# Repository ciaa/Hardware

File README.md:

Hardware
========

CIAA Hardware repository. It contains KiCad project files and documentation for each CIAA profile.

Folder structure:

[Doc](Doc): Common documents.

[PCB](PCB): KiCad PCB project files.

--[CIAA-ACC](PCB/ACC/CIAA_ACC): Xilinx Zynq XC7Z030 files.

--[EDU-FSL](PCB/EDU-FSL): EDU-CIAA-FSL (K60 MCU) files.

--[EDU-INTEL](PCB/EDU-INTEL): EDU-CIAA-INTEL (SOM Edison) files.

--[EDU-NXP](PCB/EDU-NXP): EDU-CIAA-NXP (LPC4337 MCU) files.

--[EDU-XILINX](PCB/EDU-XILINX): EDU-CIAA-XILINX (Artix7 FPGA) files.

--[FSL-MINI](PCB/FSL-MINI): CIAA-Freescale (K60 MCU) files.

--[FSL](PCB/FSL): CIAA-Freescale (K60 MCU) files.

--[NXP](PCB/NXP): CIAA-NXP (LPC4337 MCU) files.

--[PIC](PCB/PIC): CIAA-PIC (PIC32 MCU) files.

--[RX](PCB/RX): CIAA-Renesas files.

--[Safety](PCB/Safety): CIAA-Safety (RM48L952-PGE MCU) files.

--[Z3R0](PCB/Z3R0): CIAA-Z3R0 (EFM32HG MCU) files.

--[pico-CIAA](PCB/pico): pico-CIAA (LPC54102 MCU) files.

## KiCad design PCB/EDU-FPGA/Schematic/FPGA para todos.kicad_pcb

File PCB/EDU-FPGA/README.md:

# EDU-CIAA-FPGA

Here you will find KiCad design files, gerber files and documentation for this board developed by Embedded Systems application group from [UTN FR Haedo](http://www.frh.utn.edu.ar/) as part of the [CIAA project](http://www.proyecto-ciaa.com.ar/).
Also you can visit [EDU-CIAA-FPGA Wiki Page](http://www.proyecto-ciaa.com.ar/devwiki/doku.php?id=desarrollo:edu-fpga).

 - [Authors](AUTHORS.md).
 - License: [CIAA Hardware license](LICENSE).
 
## Buy the board!

The board can be acquired through Mercado Libre ecommerce platform:

 - [Option A: One payment](https://articulo.mercadolibre.com.ar/MLA-876444808-placa-desarrollo-edu-fpga-lattice-ice40hx4k-_JM#position=1&type=item&tracking_id=b1710986-8dfb-414d-ae1f-01746e770309)
 - [Option B: Pay in installments](https://articulo.mercadolibre.com.ar/MLA-878714026-placa-desarrollo-edu-fpga-lattice-ice40hx4k-cuotas-sin-int-_JM#position=2&type=item&tracking_id=b1710986-8dfb-414d-ae1f-01746e770309)
 
The board has been manufactured and is guaranteed by [Outsource SRL](http://www.outsourcesrl.com/)

## Links of interest

* [Official web page (in Spanish)](https://bit.ly/EDUFPGAok)
* [Youtube channel (in Spanish)](https://bit.ly/EDUFPGAyoutube)
* [Wiki (in Spanish)](https://bit.ly/EDUFPGAwiki)
 
## Board description

EDU-FPGA is an open source FPGA development board based on [Lattice iCE40HX4K](http://www.latticesemi.com/iCE40), and is part of **FPGA Para Todos** project, which is aimed to bring educational resources for FPGA technologies. EDU-FPGA supports [IceStorm](http://www.clifford.at/icestorm/) open source toolchain and is designed to be a low cost solution for beginners and intermediate students or professionals who wants to start studying FPGA's technologies or deepen their knowledges on this field. Currently, there are two versions of the board: v1.0 and v1.2. The following image shows both:

The board on the right is v1.2 (last version), and it has improvements on smd oscillator, USB footprint, flash memory and push-buttons, to make it more suitable for manufacture. 

More resources and information about **FPGA Para Todos** can be found on project's Wiki [here](https://gitlab.com/RamadrianG/wiki---fpga-para-todos/-/wikis/FPGA-para-Todos).

## Specifications

* Lattice iCE40HX4K FPGA (8K LUT using icestorm toolchain)
* Virtual COM port for debugging and general purpose
* NOR Flash spiFlash, 4M-bit, 4Kb Uniform Sector 
* 4 user push buttons
* 4 user leds
* 2 PMOD 2x6 interfaces
* Similar pinout than Arduino one
* Total 49 I/O pins available for the user
* 12MHz 25ppm -40C +85C clock oscillator
* USB power supply
* 80x60 cm size

### Board Arquitecture

FPGA specifications:

| **Lattice iCE40HX4K TQ144**        |**Specs**|
| ---------------------------------- | ------- |
| Logic cells                        | 3520    |
| 4Kbits Blockrams                   | 20      |
| Phase Locking Loops (PLL)          | 2       |
| DSP slices                         | No      |
| I/O pins                           | 95      |
| Differential I/O pins              | 12      |
| Package                            | TQ144   |
| Price                              | 6 USD   |

## Project directory structure

### Pinout
[Pinout diagram](Pinout/Pinout%20EDU%20FPGA.pdf) of EDU-FPGA v1.2
### Images
Contains images resources for the repository

### Schematic
Here you can find design files, like *.pro, *.sch, *.kicad_pcb. *-cache.lib, *-rescue.lib, footprints lib table, symbols lib table, [schematic.pdf](Schematic/schematic.pdf). Also, under this directory you can find:

#### BOM
[BOM of EDU-FPGA v1.2 ](Schematic/BOM/BOM.ods)

#### footprints.3dshapes
3D shapes of components

#### footprints.pretty
Footprints of all components

#### Gerbers
[Gerbers files of EDU-FPGA v1.2](Schematic/Gerbers)

#### Libraries
Libraries of component's symbols created specifically for the project

#### Panellised
Soon, 4x4 panel of EDU-FPGA v1.2 will be available in this directory.
<!--Here you can also find [Gerbers](Schematic/Panelizado/V1.2/Gerbers) of 4x4 panel.-->

#### Simbolos_EDUFPGA.pretty
Symbols of EDU-FPGA project logo

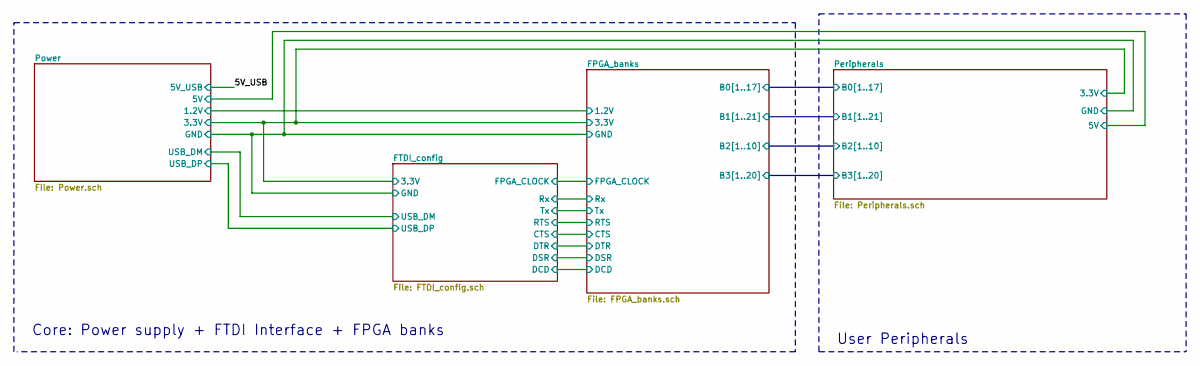
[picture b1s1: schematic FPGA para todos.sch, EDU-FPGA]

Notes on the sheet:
Core: Power supply + FTDI Interface + FPGA banks
User Peripherals

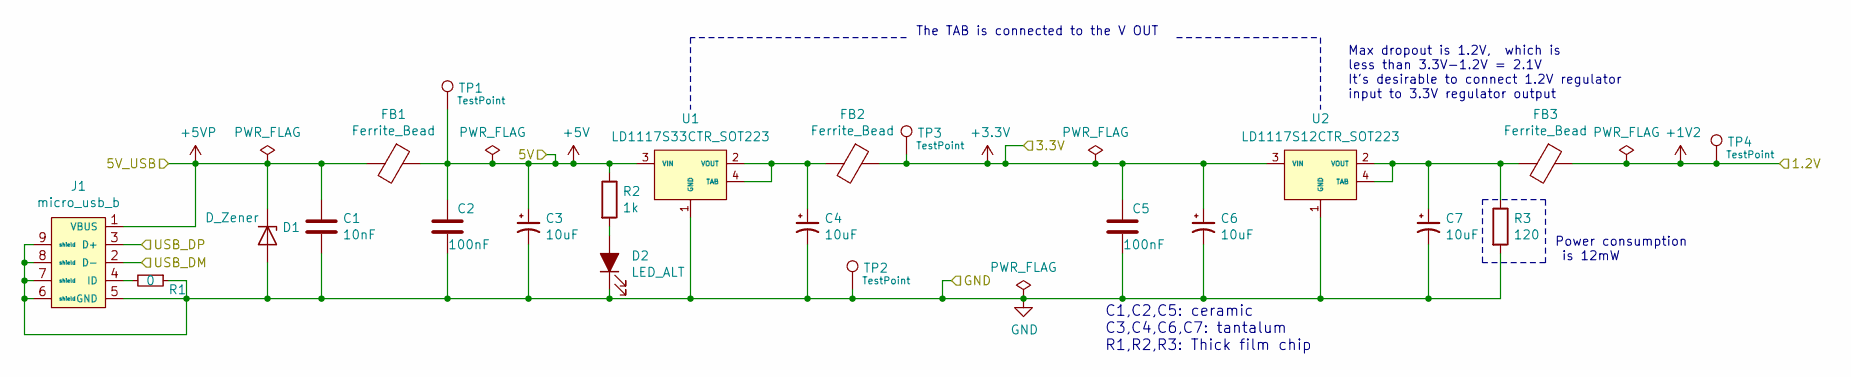
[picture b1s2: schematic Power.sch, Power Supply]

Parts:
C1: 10nF; C_0805_2012Metric_Pad1.15x1.40mm_HandSolder
C2, C5: 100nF; C_0805_2012Metric_Pad1.15x1.40mm_HandSolder
C3, C4, C6, C7: 10uF; C_0805_AVX_Tantalum
D1: D_Zener; D_SMA
D2: LED_ALT; led_0805_recommended_land_pattern
FB1, FB2, FB3: Ferrite_Bead; Ferrite_bead_0805
J1: micro_usb_b; micro_usb_b_recpt_bttm_mnt_smt_th_tabs
R1: 0; R_0805_2012Metric_Pad1.15x1.40mm_HandSolder
R2: 1k; R_0805_2012Metric_Pad1.15x1.40mm_HandSolder
R3: 120; R_0805_2012Metric_Pad1.15x1.40mm_HandSolder
TP1, TP2, TP3, TP4: TestPoint; TestPoint_Pad_D1.5mm
U1: LD1117S33CTR_SOT223; SOT-223
U2: LD1117S12CTR_SOT223; SOT-223

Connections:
+1V2: FB3.1, TP4.1; also elsewhere on the board
+3V3: C5.1, C6.1, FB2.1, TP3.1, U2.3 (VIN); also elsewhere on the board
+5V: C2.1, C3.1, FB1.1, R2.1, TP1.1, U1.3 (VIN); also elsewhere on the board
+5VP: C1.1, D1.2 (K), FB1.2, J1.1 (VBUS)
/FTDI_config/USB_DM: J1.2 (D-); also elsewhere on the board
/FTDI_config/USB_DP: J1.3 (D+); also elsewhere on the board
GND: C1.2, C2.2, C3.2, C4.2, C5.2, C6.2, C7.2, D1.1 (A), D2.2 (K), J1.5 (GND), J1.6 (shield), J1.7 (shield), J1.8 (shield), J1.9 (shield), R1.1, R3.2, TP2.1, U1.1 (GND), U2.1 (GND); also elsewhere on the board
unnamed: C4.1, FB2.2, U1.2 (VOUT), U1.4 (TAB)
unnamed: C7.1, FB3.2, R3.1, U2.2 (VOUT), U2.4 (TAB)
unnamed: D2.1 (A), R2.2
unnamed: J1.4 (ID), R1.2

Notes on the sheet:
Power consumption is 12mW
Max dropout is 1.2V, which is less than 3.3V-1.2V = 2.1V It's desirable to connect 1.2V regulator input to 3.3V regulator output
The TAB is connected to the V OUT
C1,C2,C5: ceramic C3,C4,C6,C7: tantalum R1,R2,R3: Thick film chip

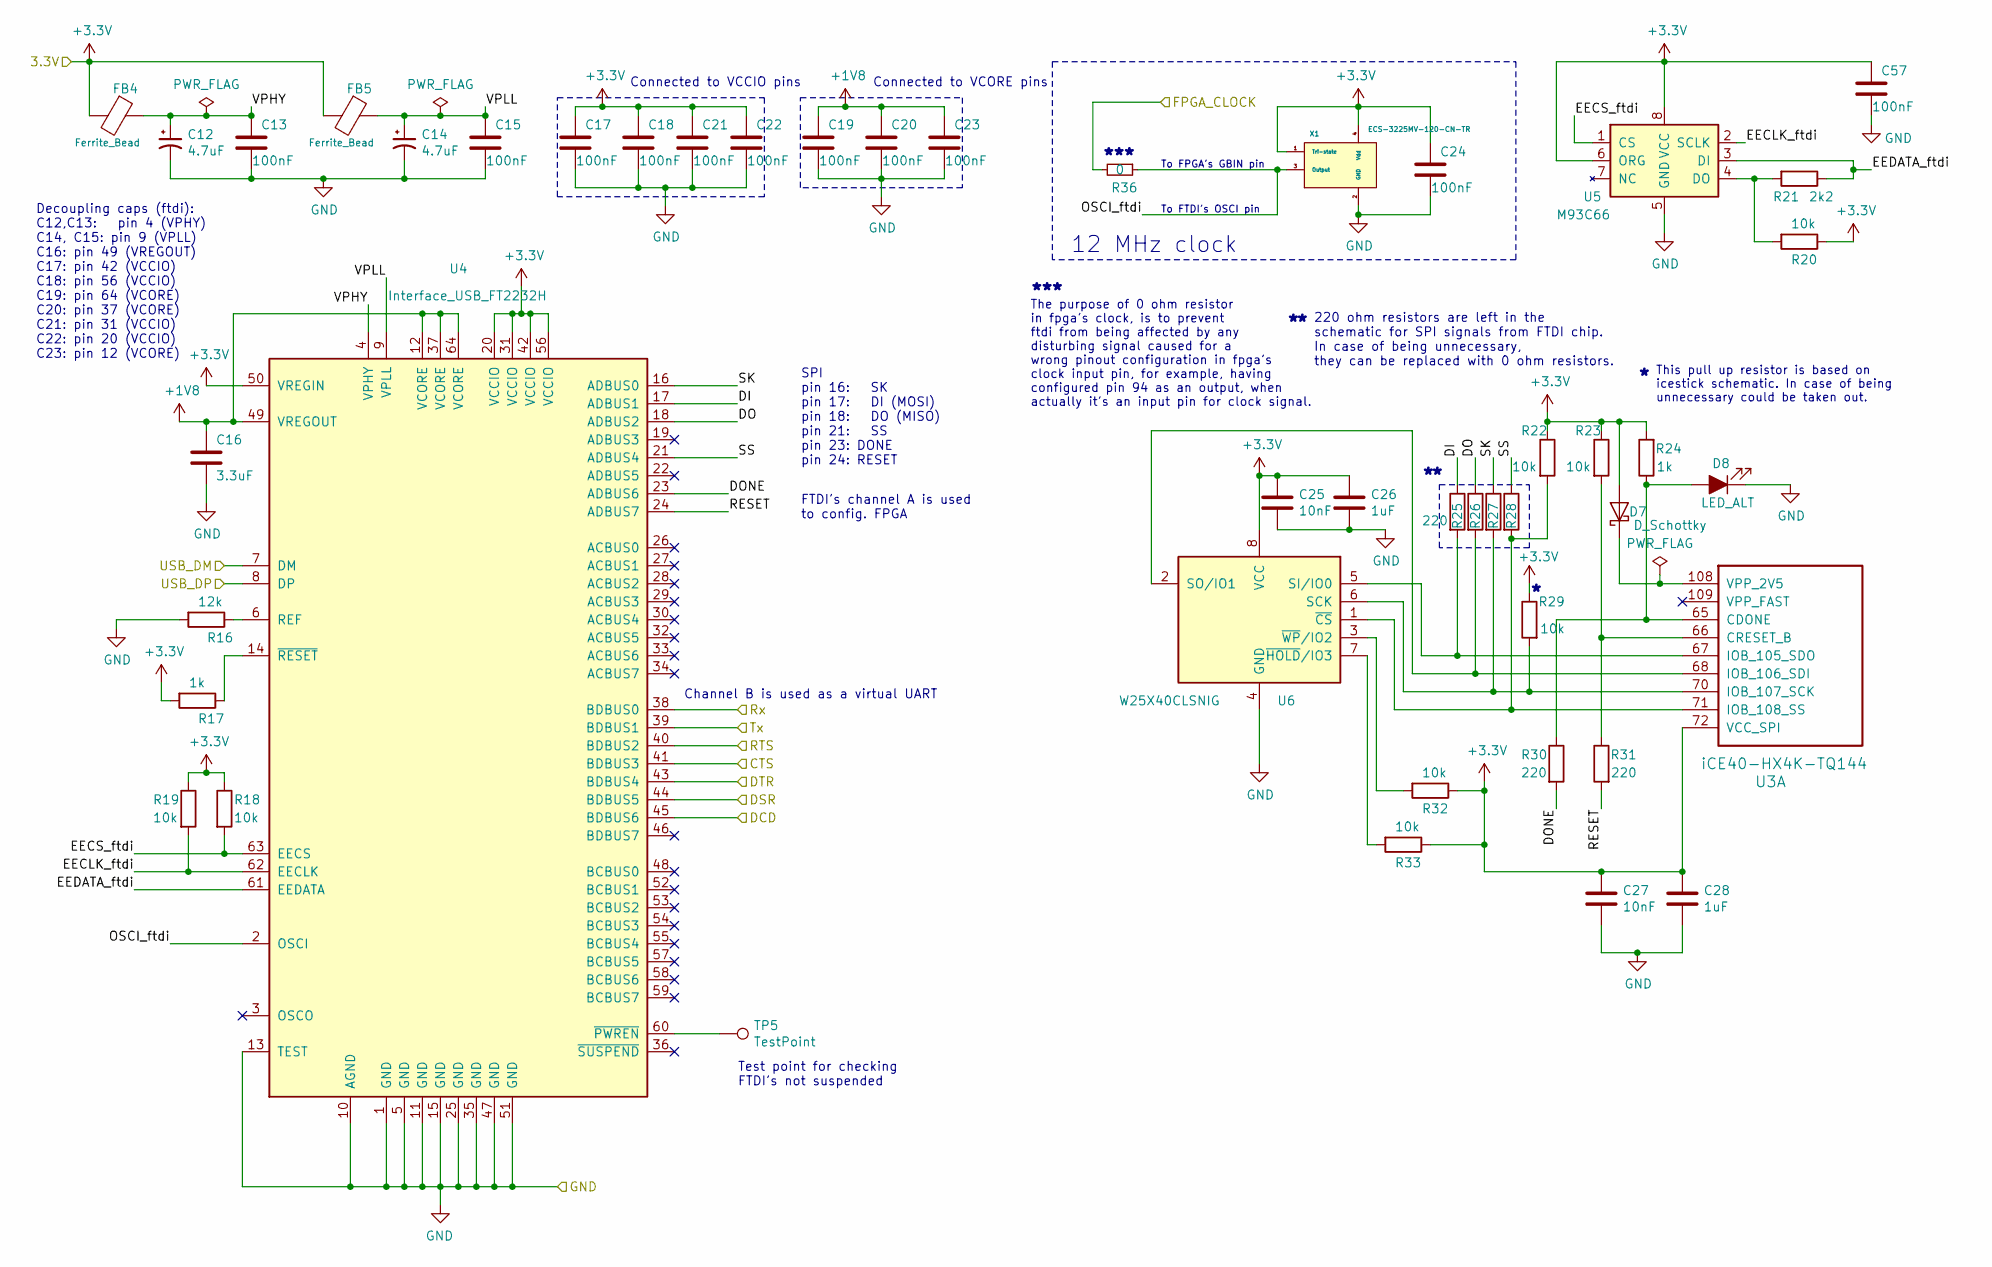
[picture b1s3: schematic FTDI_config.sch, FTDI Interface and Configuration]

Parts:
C12, C14: 4.7uF; C_0805_AVX_Tantalum
C13, C15, C17, C18, C19, C20, C21, C22, C23, C24, C57: 100nF; C_0805_2012Metric_Pad1.15x1.40mm_HandSolder
C16: 3.3uF; C_0805_2012Metric_Pad1.15x1.40mm_HandSolder
C25, C27: 10nF; C_0805_2012Metric_Pad1.15x1.40mm_HandSolder
C26, C28: 1uF; C_0805_2012Metric_Pad1.15x1.40mm_HandSolder
D7: D_Schottky; D_0805_2012Metric
D8: LED_ALT; led_0805_recommended_land_pattern
FB4, FB5: Ferrite_Bead; Ferrite_bead_0805
R16: 12k; R_0805_2012Metric_Pad1.15x1.40mm_HandSolder
R17, R24: 1k; R_0805_2012Metric_Pad1.15x1.40mm_HandSolder
R18, R19, R20, R22, R23, R29, R32, R33: 10k; R_0805_2012Metric_Pad1.15x1.40mm_HandSolder
R21: 2k2; R_0805_2012Metric_Pad1.15x1.40mm_HandSolder
R25, R26, R27, R28, R30, R31: 220; R_0805_2012Metric_Pad1.15x1.40mm_HandSolder
R36: 0; R_0805_2012Metric_Pad1.15x1.40mm_HandSolder
TP5: TestPoint; TestPoint_Pad_D1.5mm
U3: iCE40-HX4K-TQ144; QFP50P2200X2200X160-144N
U4: Interface_USB_FT2232H; LQFP-64_10x10mm_P0.5mm
U5: M93C66; m93c66_SO8N_package
U6: W25X40CLSNIG; SOIC-8
X1: ECS-3225MV-120-CN-TR; ECS-3225MV

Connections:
+1V8: C16.1, C19.1, C20.1, C23.1, U4.12 (VCORE), U4.37 (VCORE), U4.49 (VREGOUT), U4.64 (VCORE)
+3V3: C17.1, C18.1, C21.1, C22.1, C24.1, C25.1, C26.1, C27.1, C28.1, C57.1, D7.1 (A), FB4.2, FB5.2, R17.2, R18.1, R19.1, R20.1, R22.1, R23.1, R24.2, R29.1, R32.1, R33.1, U3.72 (VCC_SPI), U4.20 (VCCIO), U4.31 (VCCIO), U4.42 (VCCIO), U4.50 (VREGIN), U4.56 (VCCIO), U5.6 (ORG), U5.8 (VCC), U6.8 (VCC), X1.1 (Tri-state), X1.4 (Vdd); also elsewhere on the board
/FPGA_banks/CTS: U4.41 (BDBUS3); also elsewhere on the board
/FPGA_banks/DCD: U4.45 (BDBUS6); also elsewhere on the board
/FPGA_banks/DSR: U4.44 (BDBUS5); also elsewhere on the board
/FPGA_banks/DTR: U4.43 (BDBUS4); also elsewhere on the board
/FPGA_banks/FPGA_CLOCK: R36.2; also elsewhere on the board
/FPGA_banks/RTS: U4.40 (BDBUS2); also elsewhere on the board
/FPGA_banks/Rx: U4.38 (BDBUS0); also elsewhere on the board
/FPGA_banks/Tx: U4.39 (BDBUS1); also elsewhere on the board
/FTDI_config/DI: R25.1, U4.17 (ADBUS1)
/FTDI_config/DO: R26.1, U4.18 (ADBUS2)
/FTDI_config/DONE: R30.2, U4.23 (ADBUS6)
/FTDI_config/EECLK_ftdi: R19.2, U4.62 (EECLK), U5.2 (SCLK)
/FTDI_config/EECS_ftdi: R18.2, U4.63 (EECS), U5.1 (CS)
/FTDI_config/EEDATA_ftdi: R21.1, U4.61 (EEDATA), U5.3 (DI)
/FTDI_config/OSCI_ftdi: R36.1, U4.2 (OSCI), X1.3 (Output)
/FTDI_config/RESET: R31.2, U4.24 (ADBUS7)
/FTDI_config/SK: R27.1, U4.16 (ADBUS0)
/FTDI_config/SS: R28.1, U4.21 (ADBUS4)
/FTDI_config/USB_DM: U4.7 (DM); also elsewhere on the board
/FTDI_config/USB_DP: U4.8 (DP); also elsewhere on the board
/FTDI_config/VPHY: C12.1, C13.1, FB4.1, U4.4 (VPHY)
/FTDI_config/VPLL: C14.1, C15.1, FB5.1, U4.9 (VPLL)
GND: C12.2, C13.2, C14.2, C15.2, C16.2, C17.2, C18.2, C19.2, C20.2, C21.2, C22.2, C23.2, C24.2, C25.2, C26.2, C27.2, C28.2, C57.2, D8.2 (K), R16.2, U4.1 (GND), U4.5 (GND), U4.10 (AGND), U4.11 (GND), U4.13 (TEST), U4.15 (GND), U4.25 (GND), U4.35 (GND), U4.47 (GND), U4.51 (GND), U5.5 (GND), U6.4 (GND), X1.2 (GND); also elsewhere on the board
unnamed: D7.2 (K), U3.108 (VPP_2V5)
unnamed: D8.1 (A), R24.1, R30.1, U3.65 (CDONE)
unnamed: R16.1, U4.6 (REF)
unnamed: R17.1, U4.14 (~RESET)
unnamed: R20.2, R21.2, U5.4 (DO)
unnamed: R22.2, R28.2, U3.71 (IOB_108_SS), U6.1 (~CS)
unnamed: R23.2, R31.1, U3.66 (CRESET_B)
unnamed: R25.2, U3.67 (IOB_105_SDO), U6.5 (SI/IO0)
unnamed: R26.2, U3.68 (IOB_106_SDI), U6.2 (SO/IO1)
unnamed: R27.2, R29.2, U3.70 (IOB_107_SCK), U6.6 (SCK)
unnamed: R32.2, U6.3 (~WP~/IO2)
unnamed: R33.2, U6.7 (~HOLD~/IO3)
unnamed: TP5.1, U4.60 (~PWREN)

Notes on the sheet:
Connected to VCCIO pins
Connected to VCORE pins
FTDI's channel A is used to config. FPGA
SPI pin 16: SK pin 17: DI (MOSI) pin 18: DO (MISO) pin 21: SS pin 23: DONE pin 24: RESET
Channel B is used as a virtual UART
Test point for checking FTDI's not suspended
To FPGA's GBIN pin
To FTDI's OSCI pin
This pull up resistor is based on icestick schematic. In case of being unnecessary could be taken out.
220 ohm resistors are left in the schematic for SPI signals from FTDI chip. In case of being unnecessary, they can be replaced with 0 ohm resistors.
Decoupling caps (ftdi): C12,C13: pin 4 (VPHY) C14, C15: pin 9 (VPLL) C16: pin 49 (VREGOUT) C17: pin 42 (VCCIO) C18: pin 56 (VCCIO) C19: pin 64 (VCORE) C20: pin 37 (VCORE) C21: pin 31 (VCCIO) C22: pin 20 (VCCIO) C23: pin 12 (VCORE)
12 MHz clock
***
The purpose of 0 ohm resistor in fpga's clock, is to prevent ftdi from being affected by any disturbing signal caused for a wrong pinout configuration in fpga's clock input pin, for example, having configured pin 94 as an output, when actually it's an input pin for clock signal.

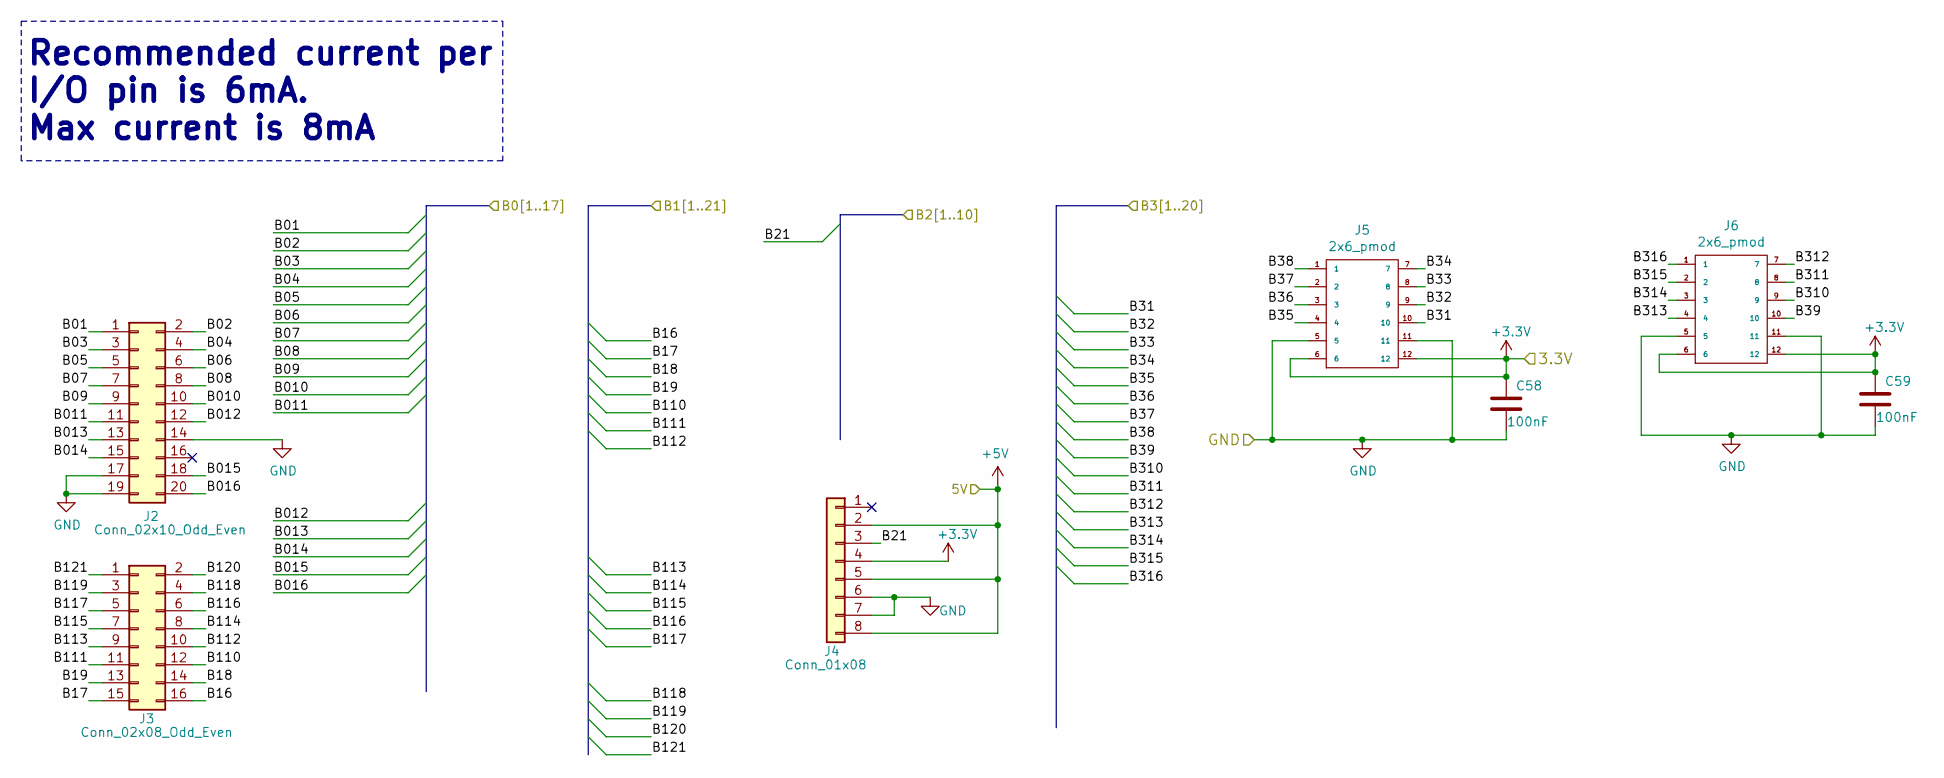
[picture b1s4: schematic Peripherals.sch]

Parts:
C58, C59: 100nF; C_0805_2012Metric_Pad1.15x1.40mm_HandSolder
J2: Conn_02x10_Odd_Even; PinSocket_2x10_P2.54mm_Vertical_mirror
J3: Conn_02x08_Odd_Even; PinSocket_2x08_P2.54mm_Vertical_mirror
J4: Conn_01x08; PinSocket_1x08_P2.54mm_Vertical
J5: 2x6_pmod; PinSocket_2x06_P2.54mm_Vertical_Mirror
J6: 2x6_pmod; PinSocket_2x06_P2.54mm_Horizontal_PMOD

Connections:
+3V3: C58.1, C59.1, J4.4, J5.6, J5.12, J6.6, J6.12; also elsewhere on the board
+5V: J4.2, J4.5, J4.8; also elsewhere on the board
/FPGA_banks/B01: J2.1; also elsewhere on the board
/FPGA_banks/B02: J2.2; also elsewhere on the board
/FPGA_banks/B03: J2.3; also elsewhere on the board
/FPGA_banks/B04: J2.4; also elsewhere on the board
/FPGA_banks/B05: J2.5; also elsewhere on the board
/FPGA_banks/B06: J2.6; also elsewhere on the board
/FPGA_banks/B07: J2.7; also elsewhere on the board
/FPGA_banks/B08: J2.8; also elsewhere on the board
/FPGA_banks/B09: J2.9; also elsewhere on the board
/FPGA_banks/B010: J2.10; also elsewhere on the board
/FPGA_banks/B011: J2.11; also elsewhere on the board
/FPGA_banks/B012: J2.12; also elsewhere on the board
/FPGA_banks/B013: J2.13; also elsewhere on the board
/FPGA_banks/B014: J2.15; also elsewhere on the board
/FPGA_banks/B015: J2.18; also elsewhere on the board
/FPGA_banks/B016: J2.20; also elsewhere on the board
/FPGA_banks/B16: J3.16; also elsewhere on the board
/FPGA_banks/B17: J3.15; also elsewhere on the board
/FPGA_banks/B18: J3.14; also elsewhere on the board
/FPGA_banks/B19: J3.13; also elsewhere on the board
/FPGA_banks/B21: J4.3; also elsewhere on the board
/FPGA_banks/B31: J5.10; also elsewhere on the board
/FPGA_banks/B32: J5.9; also elsewhere on the board
/FPGA_banks/B33: J5.8; also elsewhere on the board
/FPGA_banks/B34: J5.7; also elsewhere on the board
/FPGA_banks/B35: J5.4; also elsewhere on the board
/FPGA_banks/B36: J5.3; also elsewhere on the board
/FPGA_banks/B37: J5.2; also elsewhere on the board
/FPGA_banks/B38: J5.1; also elsewhere on the board
/FPGA_banks/B39: J6.10; also elsewhere on the board
/FPGA_banks/B110: J3.12; also elsewhere on the board
/FPGA_banks/B111: J3.11; also elsewhere on the board
/FPGA_banks/B112: J3.10; also elsewhere on the board
/FPGA_banks/B113: J3.9; also elsewhere on the board
/FPGA_banks/B114: J3.8; also elsewhere on the board
/FPGA_banks/B115: J3.7; also elsewhere on the board
/FPGA_banks/B116: J3.6; also elsewhere on the board
/FPGA_banks/B117: J3.5; also elsewhere on the board
/FPGA_banks/B118: J3.4; also elsewhere on the board
/FPGA_banks/B119: J3.3; also elsewhere on the board
/FPGA_banks/B120: J3.2; also elsewhere on the board
/FPGA_banks/B121: J3.1; also elsewhere on the board
/FPGA_banks/B310: J6.9; also elsewhere on the board
/FPGA_banks/B311: J6.8; also elsewhere on the board
/FPGA_banks/B312: J6.7; also elsewhere on the board
/FPGA_banks/B313: J6.4; also elsewhere on the board
/FPGA_banks/B314: J6.3; also elsewhere on the board
/FPGA_banks/B315: J6.2; also elsewhere on the board
/FPGA_banks/B316: J6.1; also elsewhere on the board
GND: C58.2, C59.2, J2.14, J2.17, J2.19, J4.6, J4.7, J5.5, J5.11, J6.5, J6.11; also elsewhere on the board

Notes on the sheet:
Recommended current per I/O pin is 6mA. Max current is 8mA

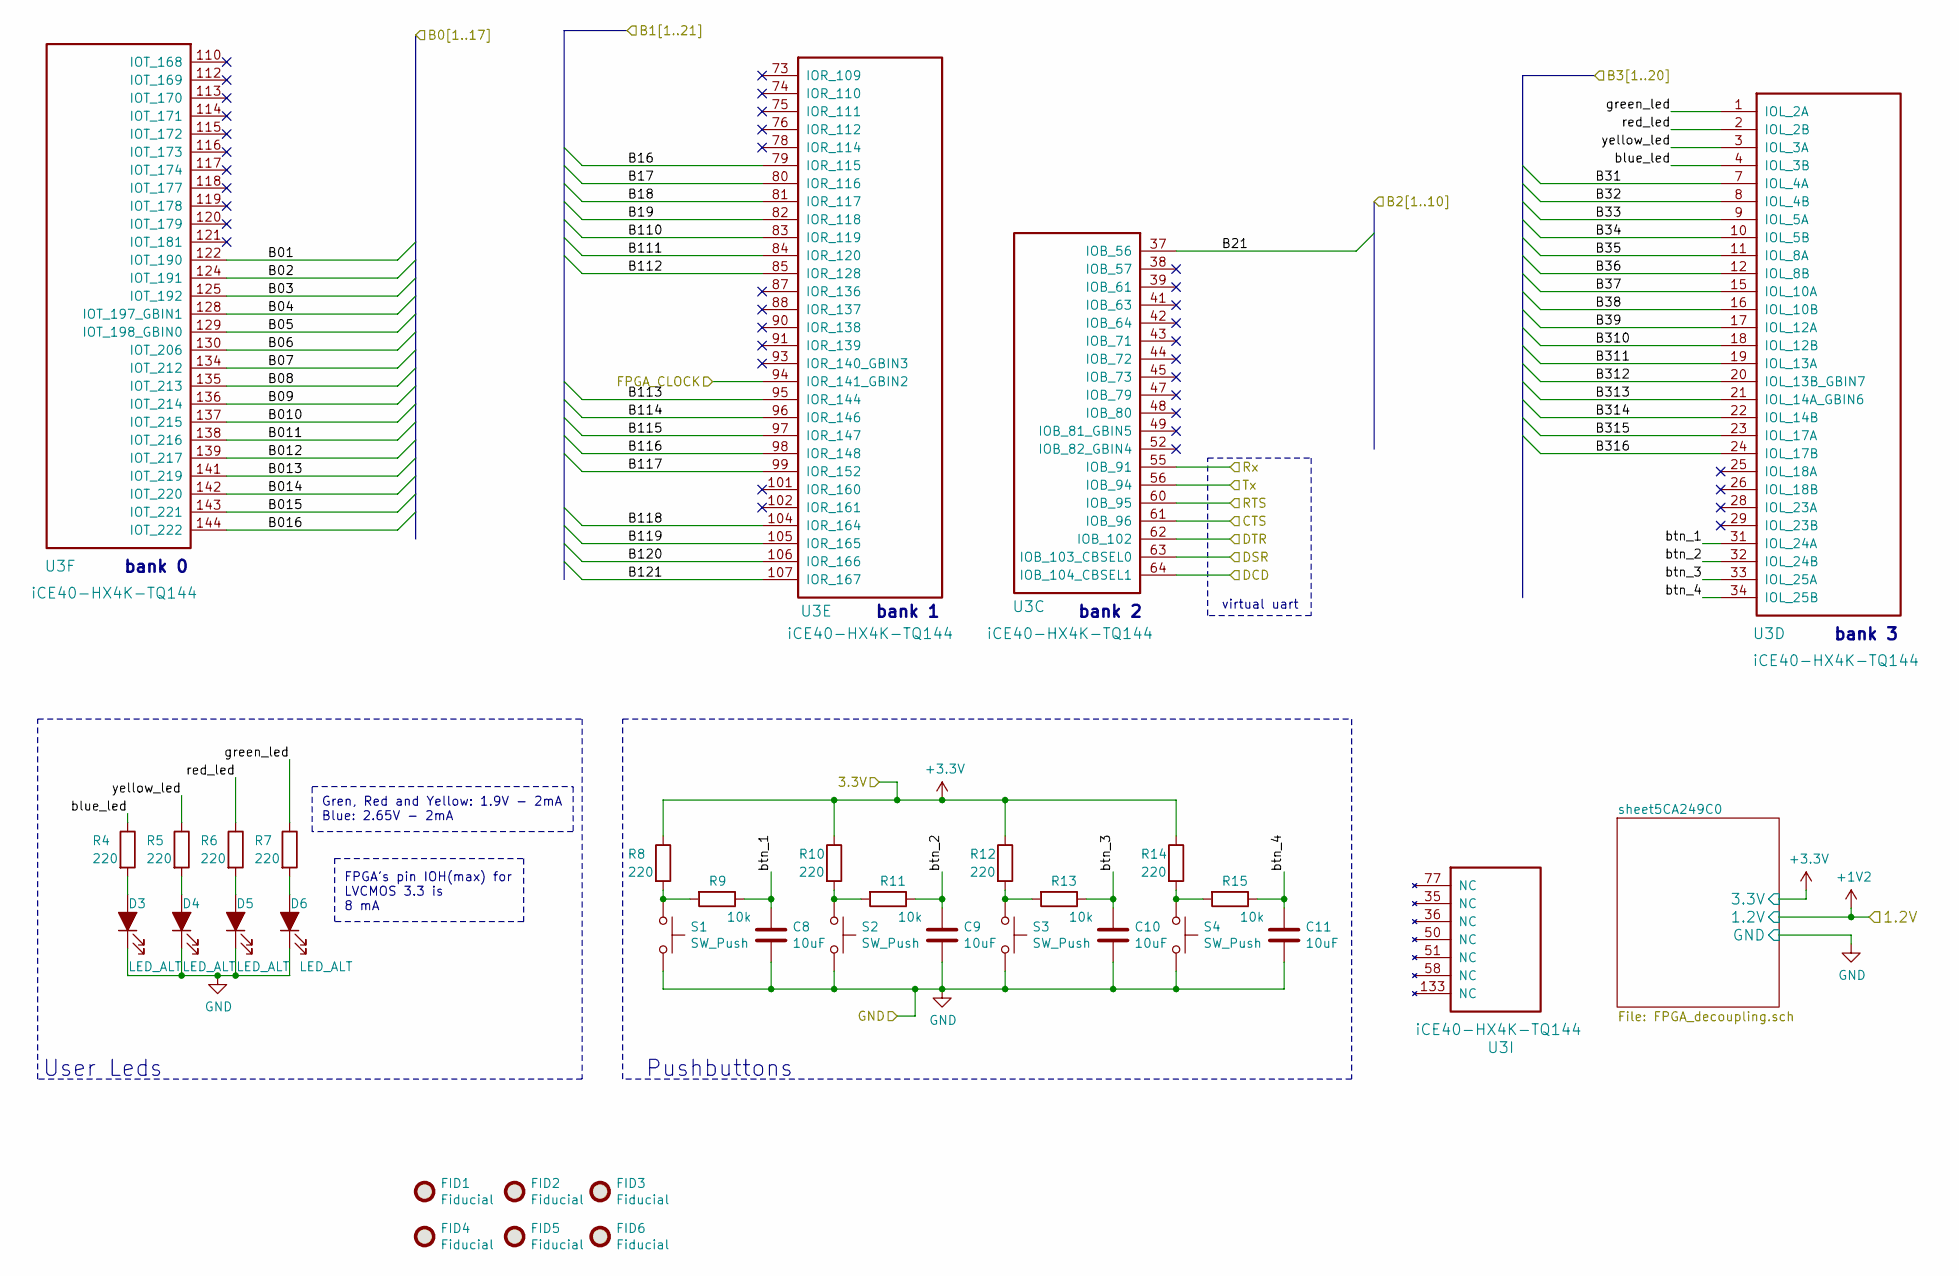
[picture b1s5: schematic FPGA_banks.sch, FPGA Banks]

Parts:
C8, C9, C10, C11: 10uF; C_0805_2012Metric_Pad1.15x1.40mm_HandSolder
D3, D4, D5, D6: LED_ALT; led_0805_recommended_land_pattern
FID1, FID2, FID3, FID4, FID5, FID6: Fiducial; Fiducial_1mm_Mask2mm
R4, R5, R6, R7, R8, R10, R12, R14: 220; R_0805_2012Metric_Pad1.15x1.40mm_HandSolder
R9, R11, R13, R15: 10k; R_0805_2012Metric_Pad1.15x1.40mm_HandSolder
S1, S2, S3, S4: SW_Push; PANASONIC_EVPBF_6MM_SMD
U3: iCE40-HX4K-TQ144; QFP50P2200X2200X160-144N

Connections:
+3V3: R8.1, R10.1, R12.1, R14.1; also elsewhere on the board
/FPGA_banks/B01: U3.122 (IOT_190); also elsewhere on the board
/FPGA_banks/B02: U3.124 (IOT_191); also elsewhere on the board
/FPGA_banks/B03: U3.125 (IOT_192); also elsewhere on the board
/FPGA_banks/B04: U3.128 (IOT_197_GBIN1); also elsewhere on the board
/FPGA_banks/B05: U3.129 (IOT_198_GBIN0); also elsewhere on the board
/FPGA_banks/B06: U3.130 (IOT_206); also elsewhere on the board
/FPGA_banks/B07: U3.134 (IOT_212); also elsewhere on the board
/FPGA_banks/B08: U3.135 (IOT_213); also elsewhere on the board
/FPGA_banks/B09: U3.136 (IOT_214); also elsewhere on the board
/FPGA_banks/B010: U3.137 (IOT_215); also elsewhere on the board
/FPGA_banks/B011: U3.138 (IOT_216); also elsewhere on the board
/FPGA_banks/B012: U3.139 (IOT_217); also elsewhere on the board
/FPGA_banks/B013: U3.141 (IOT_219); also elsewhere on the board
/FPGA_banks/B014: U3.142 (IOT_220); also elsewhere on the board
/FPGA_banks/B015: U3.143 (IOT_221); also elsewhere on the board
/FPGA_banks/B016: U3.144 (IOT_222); also elsewhere on the board
/FPGA_banks/B16: U3.79 (IOR_115); also elsewhere on the board
/FPGA_banks/B17: U3.80 (IOR_116); also elsewhere on the board
/FPGA_banks/B18: U3.81 (IOR_117); also elsewhere on the board
/FPGA_banks/B19: U3.82 (IOR_118); also elsewhere on the board
/FPGA_banks/B21: U3.37 (IOB_56); also elsewhere on the board
/FPGA_banks/B31: U3.7 (IOL_4A); also elsewhere on the board
/FPGA_banks/B32: U3.8 (IOL_4B); also elsewhere on the board
/FPGA_banks/B33: U3.9 (IOL_5A); also elsewhere on the board
/FPGA_banks/B34: U3.10 (IOL_5B); also elsewhere on the board
/FPGA_banks/B35: U3.11 (IOL_8A); also elsewhere on the board
/FPGA_banks/B36: U3.12 (IOL_8B); also elsewhere on the board
/FPGA_banks/B37: U3.15 (IOL_10A); also elsewhere on the board
/FPGA_banks/B38: U3.16 (IOL_10B); also elsewhere on the board
/FPGA_banks/B39: U3.17 (IOL_12A); also elsewhere on the board
/FPGA_banks/B110: U3.83 (IOR_119); also elsewhere on the board
/FPGA_banks/B111: U3.84 (IOR_120); also elsewhere on the board
/FPGA_banks/B112: U3.85 (IOR_128); also elsewhere on the board
/FPGA_banks/B113: U3.95 (IOR_144); also elsewhere on the board
/FPGA_banks/B114: U3.96 (IOR_146); also elsewhere on the board
/FPGA_banks/B115: U3.97 (IOR_147); also elsewhere on the board
/FPGA_banks/B116: U3.98 (IOR_148); also elsewhere on the board
/FPGA_banks/B117: U3.99 (IOR_152); also elsewhere on the board
/FPGA_banks/B118: U3.104 (IOR_164); also elsewhere on the board
/FPGA_banks/B119: U3.105 (IOR_165); also elsewhere on the board
/FPGA_banks/B120: U3.106 (IOR_166); also elsewhere on the board
/FPGA_banks/B121: U3.107 (IOR_167); also elsewhere on the board
/FPGA_banks/B310: U3.18 (IOL_12B); also elsewhere on the board
/FPGA_banks/B311: U3.19 (IOL_13A); also elsewhere on the board
/FPGA_banks/B312: U3.20 (IOL_13B_GBIN7); also elsewhere on the board
/FPGA_banks/B313: U3.21 (IOL_14A_GBIN6); also elsewhere on the board
/FPGA_banks/B314: U3.22 (IOL_14B); also elsewhere on the board
/FPGA_banks/B315: U3.23 (IOL_17A); also elsewhere on the board
/FPGA_banks/B316: U3.24 (IOL_17B); also elsewhere on the board
/FPGA_banks/CTS: U3.61 (IOB_96); also elsewhere on the board
/FPGA_banks/DCD: U3.64 (IOB_104_CBSEL1); also elsewhere on the board
/FPGA_banks/DSR: U3.63 (IOB_103_CBSEL0); also elsewhere on the board
/FPGA_banks/DTR: U3.62 (IOB_102); also elsewhere on the board
/FPGA_banks/FPGA_CLOCK: U3.94 (IOR_141_GBIN2); also elsewhere on the board
/FPGA_banks/RTS: U3.60 (IOB_95); also elsewhere on the board
/FPGA_banks/Rx: U3.55 (IOB_91); also elsewhere on the board
/FPGA_banks/Tx: U3.56 (IOB_94); also elsewhere on the board
/FPGA_banks/blue_led: R4.1, U3.4 (IOL_3B)
/FPGA_banks/btn_1: C8.1, R9.1, U3.31 (IOL_24A)
/FPGA_banks/btn_2: C9.1, R11.1, U3.32 (IOL_24B)
/FPGA_banks/btn_3: C10.1, R13.1, U3.33 (IOL_25A)
/FPGA_banks/btn_4: C11.1, R15.1, U3.34 (IOL_25B)
/FPGA_banks/green_led: R7.1, U3.1 (IOL_2A)
/FPGA_banks/red_led: R6.1, U3.2 (IOL_2B)
/FPGA_banks/yellow_led: R5.1, U3.3 (IOL_3A)
GND: C8.2, C9.2, C10.2, C11.2, D3.2 (K), D4.2 (K), D5.2 (K), D6.2 (K), S1.2, S2.2, S3.2, S4.2; also elsewhere on the board
unnamed: D3.1 (A), R4.2
unnamed: D4.1 (A), R5.2
unnamed: D5.1 (A), R6.2
unnamed: D6.1 (A), R7.2
unnamed: R8.2, R9.2, S1.1
unnamed: R10.2, R11.2, S2.1
unnamed: R12.2, R13.2, S3.1
unnamed: R14.2, R15.2, S4.1

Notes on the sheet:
bank 1
bank 0
virtual uart
bank 2
bank 3
Gren, Red and Yellow: 1.9V - 2mA Blue: 2.65V - 2mA
FPGA's pin IOH(max) for LVCMOS 3.3 is 8 mA
User Leds
Pushbuttons

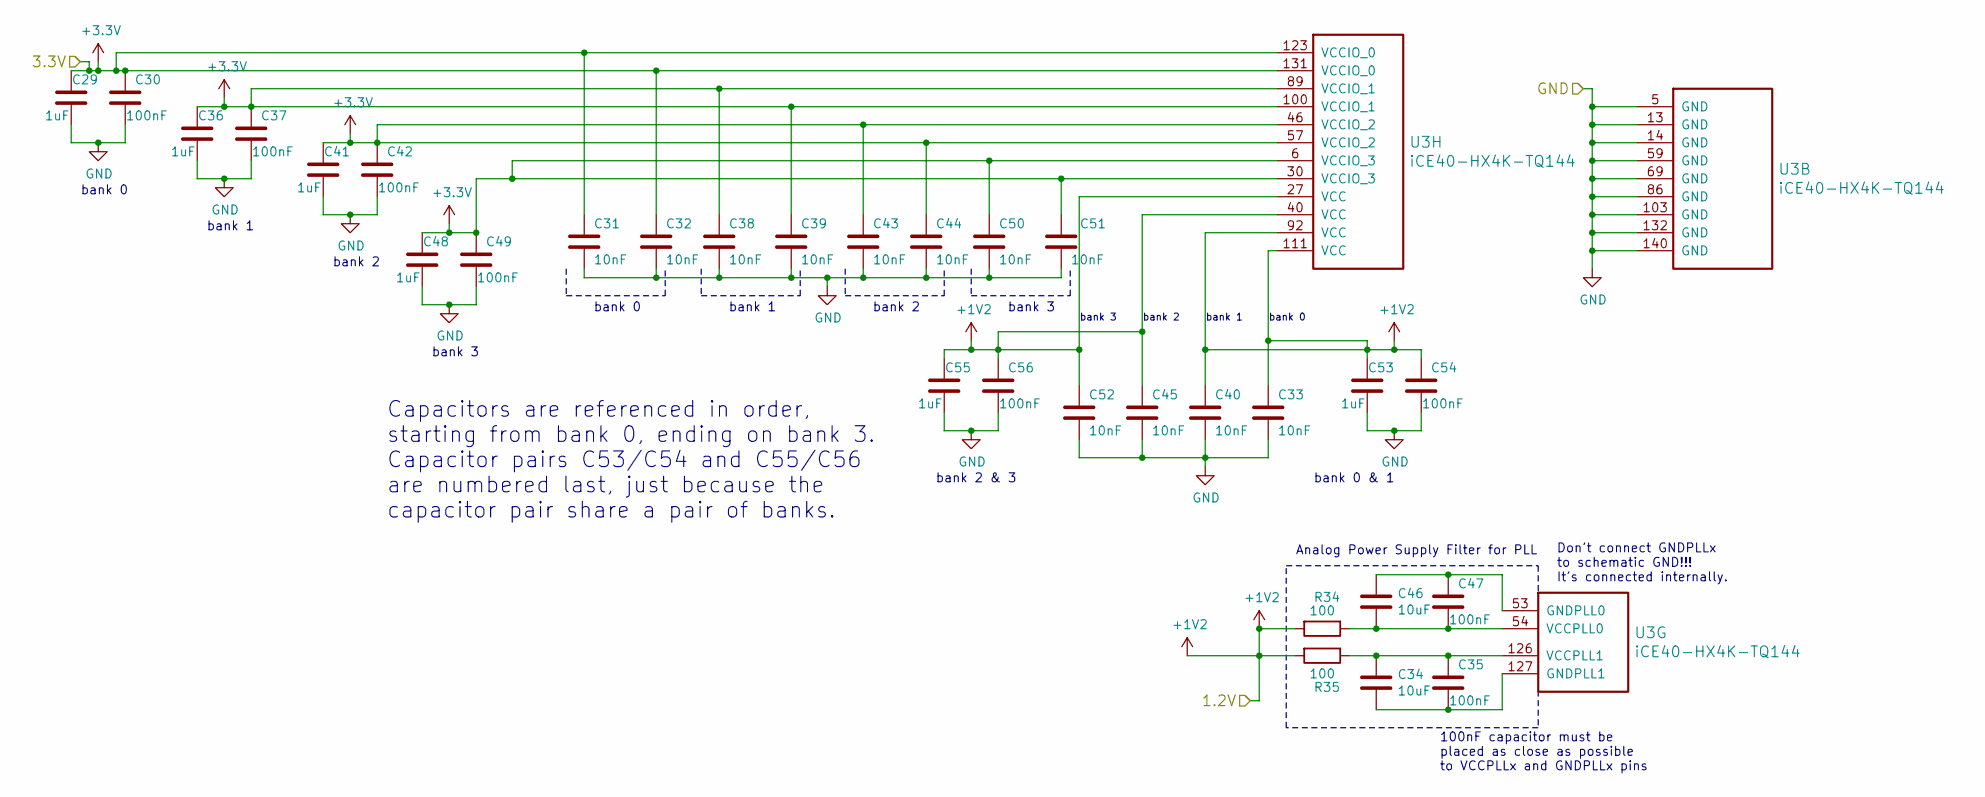
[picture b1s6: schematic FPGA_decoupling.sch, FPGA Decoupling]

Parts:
C29, C36, C41, C48, C53, C55: 1uF; C_0805_2012Metric_Pad1.15x1.40mm_HandSolder
C30, C35, C37, C42, C47, C49, C54, C56: 100nF; C_0805_2012Metric_Pad1.15x1.40mm_HandSolder
C31, C32, C33, C38, C39, C40, C43, C44, C45, C50, C51, C52: 10nF; C_0805_2012Metric_Pad1.15x1.40mm_HandSolder
C34, C46: 10uF; C_0805_2012Metric_Pad1.15x1.40mm_HandSolder
R34, R35: 100; R_0805_2012Metric_Pad1.15x1.40mm_HandSolder
U3: iCE40-HX4K-TQ144; QFP50P2200X2200X160-144N

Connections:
+1V2: C33.1, C40.1, C45.1, C52.1, C53.1, C54.1, C55.1, C56.1, R34.2, R35.2, U3.27 (VCC), U3.40 (VCC), U3.92 (VCC), U3.111 (VCC); also elsewhere on the board
+3V3: C29.1, C30.1, C31.1, C32.1, C36.1, C37.1, C38.1, C39.1, C41.1, C42.1, C43.1, C44.1, C48.1, C49.1, C50.1, C51.1, U3.6 (VCCIO_3), U3.30 (VCCIO_3), U3.46 (VCCIO_2), U3.57 (VCCIO_2), U3.89 (VCCIO_1), U3.100 (VCCIO_1), U3.123 (VCCIO_0), U3.131 (VCCIO_0); also elsewhere on the board
GND: C29.2, C30.2, C31.2, C32.2, C33.2, C36.2, C37.2, C38.2, C39.2, C40.2, C41.2, C42.2, C43.2, C44.2, C45.2, C48.2, C49.2, C50.2, C51.2, C52.2, C53.2, C54.2, C55.2, C56.2, U3.5 (GND), U3.13 (GND), U3.14 (GND), U3.59 (GND), U3.69 (GND), U3.86 (GND), U3.103 (GND), U3.132 (GND), U3.140 (GND); also elsewhere on the board
unnamed: C34.1, C35.1, R35.1, U3.126 (VCCPLL1)
unnamed: C34.2, C35.2, U3.127 (GNDPLL1)
unnamed: C46.1, C47.1, U3.53 (GNDPLL0)
unnamed: C46.2, C47.2, R34.1, U3.54 (VCCPLL0)

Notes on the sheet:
bank 0
bank 1
bank 2
bank 3
bank 2 & 3
bank 0 & 1
Analog Power Supply Filter for PLL
100nF capacitor must be placed as close as possible to VCCPLLx and GNDPLLx pins
Don't connect GNDPLLx to schematic GND!!! It's connected internally.
Capacitors are referenced in order, starting from bank 0, ending on bank 3. Capacitor pairs C53/C54 and C55/C56 are numbered last, just because the capacitor pair share a pair of banks.
